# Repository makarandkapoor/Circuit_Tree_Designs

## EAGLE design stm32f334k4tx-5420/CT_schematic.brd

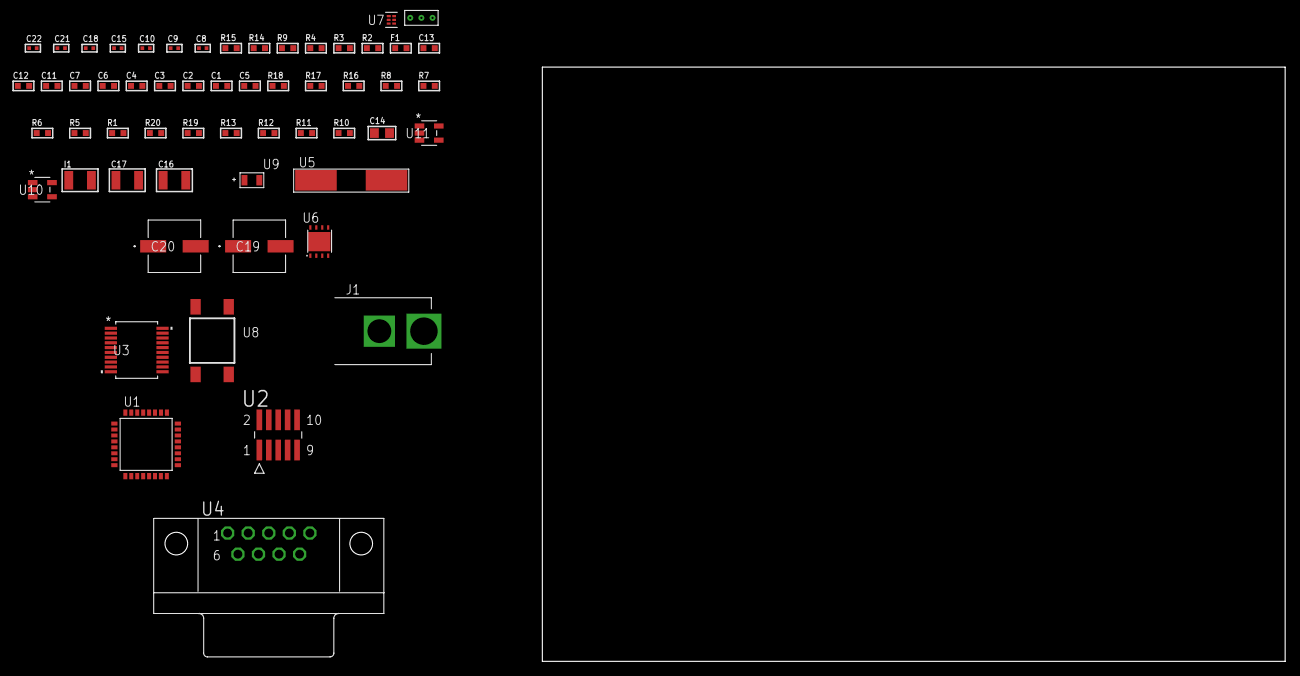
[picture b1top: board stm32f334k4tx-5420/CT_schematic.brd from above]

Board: 2 copper layers, 100.0 x 80.0 mm, 57 parts (0 on the bottom side), 40 nets, no tracks yet.

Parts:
C1, C2, C3, C4: 1e-07; C0603
C5: 4.7e-06; C0603
C6: 1e-08; C0603
C7, C11, C12, C13: 1e-06; C0603
C8, C9: 1e-11; C0402
C10, C18: 1e-07; C0402
C14: 4.7e-06; C0805
C15, C21, C22: 1e-08; C0402
C16, C17: 1e-05; C1210
C19, C20: 0.0001; EXV-9H
F1: 240.0; L0603
I1: 1.5e-05; L1210
J1: PJ-037B; PJ-037B_PACKAGE
R1, R5, R6, R7, R8, R16, R17: 10000.0; R0603
R2, R15: 1000.0; R0603
R3: 1270.0; R0603
R4: 4700.0; R0603
R9: 5.0; R0603
R10, R11, R12, R13: 100000.0; R0603
R14: 1500.0; R0603
R18: 18000.0; R0603
R19: 470000.0; R0603
R20: 120000.0; R0603
U1: STM32F334K4T6; LQFP32
U2: FTSH-105-01-L-DV-K; SAMTEC_FTSH-105-01-L-DV-K
U3: MAX3218EAP+T; SSOP-20
U4: 182-009-113R531; 182-009-MALE
U5: ABLS-25.000MHZ-B2F-T
U6: LP3878SDX-ADJ/NOPB; WSON-8
U7: TPS3895ADRYR; SON-6
U8: 4-1437565-2; SW_4-1437565-2
U9: Q65110A2395; LGM67K-G1J2-24-Z
U10, U11: nc7sz125m5x; NC7SZ125M5X
U12: Dummy; DUMMY_PACKAGE_115

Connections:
CLK_CRYSTAL_U1_2: C8.1, U1.2, U5.1
CLK_CRYSTAL_U1_3: C9.1, U1.3, U5.2
GND: C1.2, C2.2, C3.2, C4.2, C5.2, C6.2, C7.2, C8.2, C9.2, C10.2, C11.2, C12.2, C13.2, C15.2, C16.2, C17.2, C18.2, C19.2, C20.2, C21.2, C22.2, J1.2, R2.2, R5.2, R9.2, R15.2, R18.2, R20.2, U1.16, U1.32, U2.3, U2.5, U3.5, U3.17, U3.20, U4.5, U6.3, U6.PAD, U7.2, U9.C, U10.2, U10.3, U11.1, U11.3, U12.1
NET_U1_4: R4.1, U1.4, U11.4
NET_U1_5: C6.1, C7.1, F1.1, U1.5
NET_U1_29: R3.1, U1.29, U9.A
NET_U1_30: R1.1, U1.30, U8.3, U8.4
NET_U1_31: R5.1, U1.31
NET_U2_9: R9.1, U2.9
NET_U3_1: I1.1, U3.1
NET_U3_2: R10.1, U3.2
NET_U3_3: R11.1, U3.3
NET_U3_4: R12.1, U3.4
NET_U3_15: C13.1, U3.15
NET_U3_16: C14.2, U3.16
NET_U3_18: C14.1, U3.18
NET_U3_19: C12.1, U3.19
NET_U4_2: U3.12, U4.2
NET_U4_3: U3.14, U4.3
NET_U4_7: U3.11, U4.7
NET_U4_8: U3.13, U4.8
NET_U6_1: C15.1, U6.1
NET_U6_6: R14.2, R15.1, U6.6
NET_U6_8: R13.1, U6.8
NET_U7_1: R17.1, R18.1, U7.1
NET_U7_3: R19.2, R20.1, U7.3
NET_U7_4: R16.1, U7.4, U10.4, U11.2
NET_U8_1: R2.1, U8.1, U8.2
PROC_ADC1_IN1: U1.6, U12.3
PROC_ADC1_IN2: U1.7, U12.2
PROC_SYS_JTCK_SWCLK: R7.1, U1.24, U2.4
PROC_SYS_JTDO_TRACESWO: U1.26, U2.6
PROC_SYS_JTMS_SWDIO: R8.1, U1.23, U2.2
PROC_USART1_CTS: U1.21, U3.8
PROC_USART1_RTS: U1.22, U3.10
PROC_USART1_RX: U1.20, U3.9
PROC_USART1_TX: U1.19, U3.7
RST_OUT_U2_JTAG_RST_B: R6.1, U2.10, U10.1
VCC_S1_14V8: C16.1, C19.1, C20.1, J1.1, R13.2, U6.4
VCC_TIER1_2V5: C1.1, C2.1, C3.1, C4.1, C5.1, C10.1, C11.1, C17.1, C18.1, C21.1, C22.1, F1.2, I1.2, R1.2, R3.2, R4.2, R6.2, R7.2, R8.2, R10.2, R11.2, R12.2, R14.1, R16.2, R17.2, R19.1, U1.1, U1.17, U2.1, U3.6, U6.5, U7.6, U10.5, U11.5

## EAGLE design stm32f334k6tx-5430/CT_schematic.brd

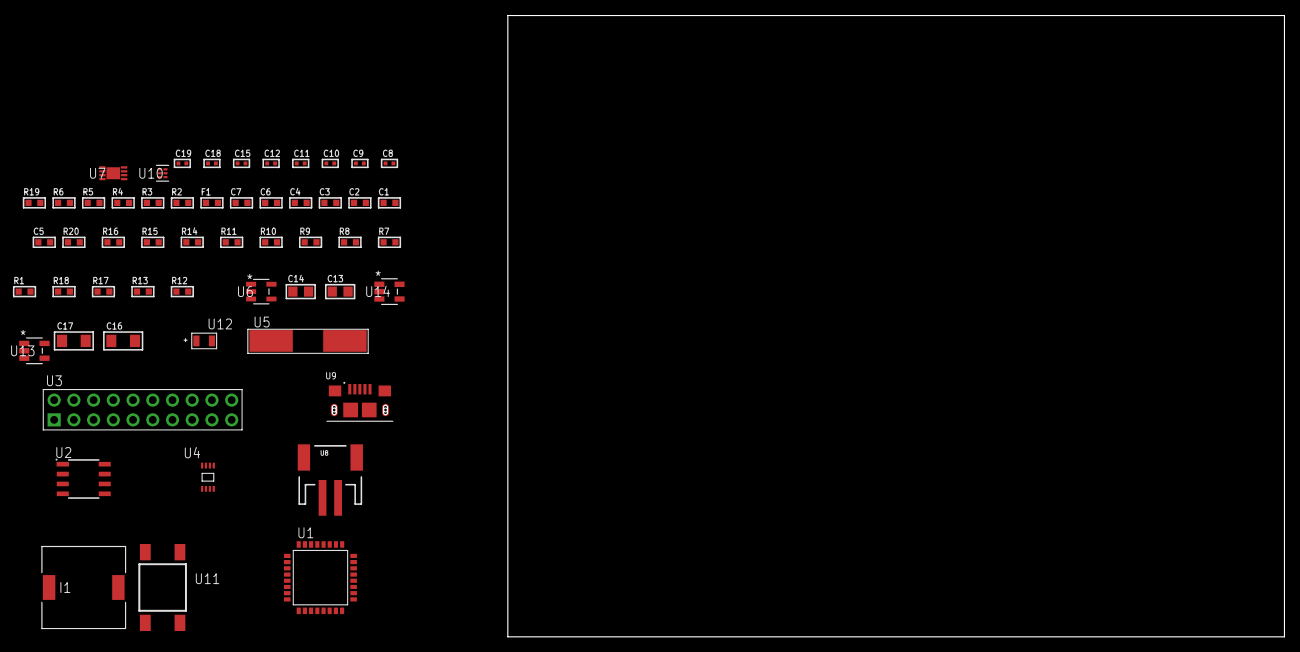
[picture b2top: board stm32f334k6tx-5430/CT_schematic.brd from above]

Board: 2 copper layers, 122.6 x 80.0 mm, 55 parts (0 on the bottom side), 32 nets, no tracks yet.

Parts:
C1, C2, C3, C4: 1e-07; C0603
C5: 4.7e-06; C0603
C6: 1e-08; C0603
C7: 1e-06; C0603
C8, C9: 1e-11; C0402
C10, C12, C18, C19: 1e-08; C0402
C11, C15: 1e-07; C0402
C13, C14: 1e-05; C0805
C16, C17: 1e-05; C1206
F1: 240.0; L0603
I1: 3.8e-06; DR1040
R1, R7, R8, R9, R10, R11, R14, R15, R20: 10000.0; R0603
R2: 1000.0; R0603
R3: 1270.0; R0603
R4: 4700.0; R0603
R5, R6: 2200.0; R0603
R12: 309473.68421053; R0603
R13: 1000000.0; R0603
R16: 18000.0; R0603
R17: 470000.0; R0603
R18: 120000.0; R0603
R19: 2000.0; R0603
U1: STM32F334K6T6; LQFP32
U2: AT25256B-SSHL-T; SOIC-8
U3: TST-110-05-T-D-RA
U4: 24AA02T-I/MNY; TDFN-8/6MM
U5: ABLS-25.000MHZ-B2F-T
U6: ltc3406es5; TSOT-23-5
U7: MCP73831T-2ACI/MC; DFN8_2X3MC
U8: S2B-PH-SM4-TB(LF)(SN); JST-2-SMD
U9: 10118193-0001LF; FCI_10118193-0001LF
U10: TPS3895ADRYR; SON-6
U11: 4-1437565-2; SW_4-1437565-2
U12: Q65110A2395; LGM67K-G1J2-24-Z
U13, U14: nc7sz125m5x; NC7SZ125M5X

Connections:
CLK_CRYSTAL_U1_2: C8.1, U1.2, U5.1
CLK_CRYSTAL_U1_3: C9.1, U1.3, U5.2
GND: C1.2, C2.2, C3.2, C4.2, C5.2, C6.2, C7.2, C8.2, C9.2, C10.2, C11.2, C12.2, C13.2, C14.1, C14.2, C15.2, C16.2, C17.2, C18.2, C19.2, R2.2, R7.2, R12.2, R16.2, R18.2, R19.2, U1.16, U1.32, U2.4, U3.4, U3.6, U3.8, U3.10, U3.12, U3.14, U3.16, U3.18, U3.20, U4.4, U4.7, U6.2, U7.6, U7.9, U8.2, U9.5, U9.6, U9.7, U9.8, U9.9, U10.2, U12.C, U13.2, U13.3, U14.1, U14.3
INPUT_USBPOWER_5V: C16.1, R20.2, U7.1, U7.2, U9.1
NET_U1_4: R4.1, U1.4, U14.4
NET_U1_5: C6.1, C7.1, F1.1, U1.5
NET_U1_25: R5.1, U1.25, U4.6
NET_U1_28: R3.1, U1.28, U12.A
NET_U1_29: R1.1, U1.29, U11.3, U11.4
NET_U1_30: R6.1, U1.30, U4.5
NET_U1_31: R7.1, U1.31
NET_U2_3: R8.1, U2.3
NET_U2_7: R10.1, U2.7
NET_U6_3: I1.1, U6.3
NET_U6_5: R12.1, R13.1, U6.5
NET_U6_ATNET_3: I1.2, R13.2
NET_U7_5: R20.1, U7.5
NET_U7_8: R19.1, U7.8
NET_U10_1: R15.1, R16.1, U10.1
NET_U10_3: R17.2, R18.1, U10.3
NET_U10_4: R14.1, U10.4, U13.4, U14.2
NET_U11_1: R2.1, U11.1, U11.2
PROC_SPI1_MISO: U1.12, U2.2
PROC_SPI1_MOSI: U1.13, U2.5
PROC_SPI1_NSS: R9.1, U1.10, U2.1
PROC_SPI1_SCK: U1.11, U2.6
PROC_SYS_JTCK_SWCLK: U1.24, U3.9
PROC_SYS_JTDO_TRACESWO: U1.26, U3.13
PROC_SYS_JTMS_SWDIO: U1.23, U3.7
RST_OUT_U3_SRESET_B: R11.1, U3.15, U13.1
VCC_S1_3V7: C13.1, C17.1, U6.4, U7.3, U7.4, U8.1
VCC_TIER1_2V5: C1.1, C2.1, C3.1, C4.1, C5.1, C10.1, C11.1, C12.1, C14.2, C15.1, C18.1, C19.1, F1.2, I1.2, R1.2, R3.2, R4.2, R5.2, R6.2, R8.2, R9.2, R10.2, R11.2, R13.2, R14.2, R15.2, R17.1, U1.1, U1.17, U2.8, U3.1, U4.8, U10.6, U13.5, U14.5

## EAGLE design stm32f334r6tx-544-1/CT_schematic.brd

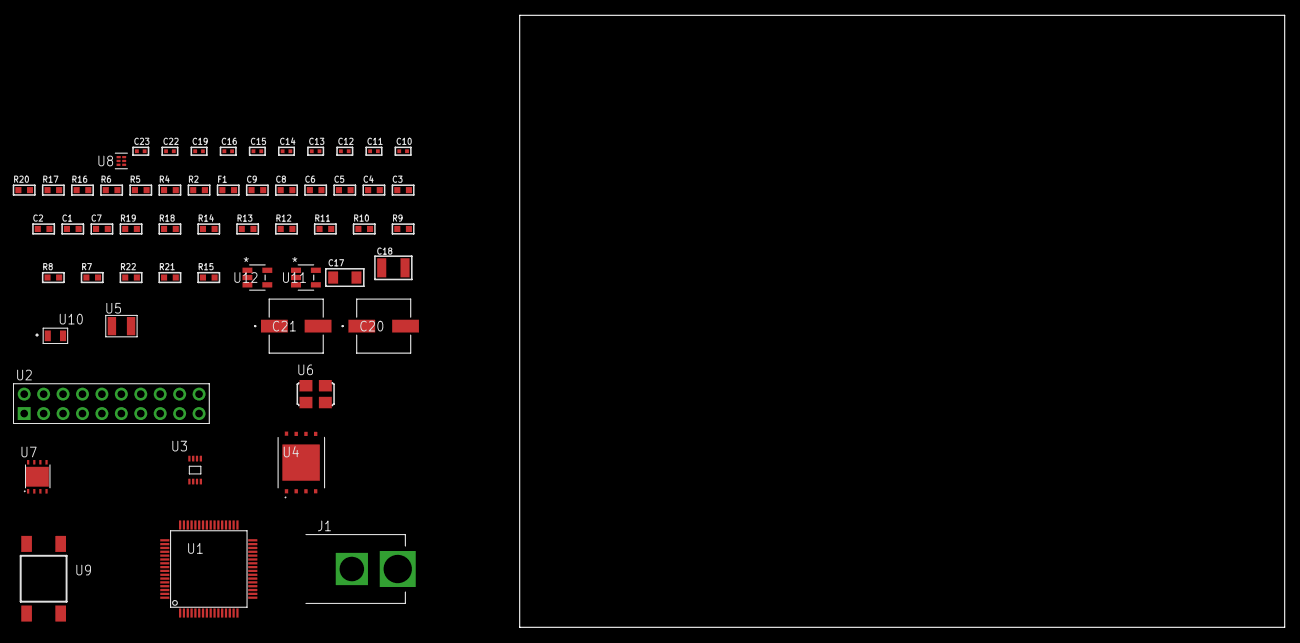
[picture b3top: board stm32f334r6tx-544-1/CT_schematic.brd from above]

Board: 2 copper layers, 100.0 x 80.0 mm, 57 parts (0 on the bottom side), 32 nets, no tracks yet.

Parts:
C1, C9: 1e-06; C0603
C2, C3, C4, C5, C6: 1e-07; C0603
C7: 4.7e-06; C0603
C8: 1e-08; C0603
C10, C11: 1e-11; C0402
C12, C19: 1e-07; C0402
C13, C14, C15, C16, C22, C23: 1e-08; C0402
C17: 1e-05; C1206
C18: 1e-05; C1210
C20, C21: 0.0001; EXV-9H
F1: 240.0; L0603
J1: PJ-037B; PJ-037B_PACKAGE
R2, R17: 1000.0; R0603
R4: 4700.0; R0603
R5, R6: 2200.0; R0603
R7, R8, R9, R10, R11, R12, R13, R14, R18, R19: 10000.0; R0603
R15: 100000.0; R0603
R16: 2231.0; R0603
R20: 9100.0; R0603
R21: 680000.0; R0603
R22: 120000.0; R0603
U1: STM32F334R6T6; LQFP64
U2: TST-110-05-T-D-RA
U3: 24AA64T-I/MNY; TDFN-8/6MM
U4: S25FL128SDPNFI001; WNG008
U5: ABS07-32.768KHZ-7-T
U6: ASFL1-25MHZ-NCS; ASFL1
U7: LP3878SDX-ADJ/NOPB; WSON-8
U8: TPS3895ADRYR; SON-6
U9: 4-1437565-2; SW_4-1437565-2
U10: Q65110A2395; LGM67K-G1J2-24-Z
U11, U12: nc7sz125m5x; NC7SZ125M5X

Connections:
CLK_CRYSTAL_U1_3: C10.1, U1.3, U5.1
CLK_CRYSTAL_U1_4: C11.1, U1.4, U5.2
CLK_U1_5: U1.5, U6.3
GND: C1.2, C2.2, C3.2, C4.2, C5.2, C6.2, C7.2, C8.2, C9.2, C10.2, C11.2, C12.2, C13.2, C14.2, C15.2, C16.2, C17.2, C18.2, C19.2, C20.2, C21.2, C22.2, C23.2, J1.2, R2.2, R7.2, R11.2, R17.2, R20.2, R22.2, U1.12, U1.18, U1.31, U1.47, U1.63, U2.4, U2.6, U2.8, U2.10, U2.12, U2.14, U2.16, U2.18, U2.20, U3.4, U3.7, U4.4, U4.PAD, U6.2, U7.3, U7.PAD, U8.2, U10.C, U11.2, U11.3, U12.1, U12.3
NET_U1_7: R4.1, U1.7, U12.4
NET_U1_13: C8.1, C9.1, F1.1, U1.13
NET_U1_50: R5.1, U1.50, U3.6
NET_U1_59: R6.1, U1.59, U3.5
NET_U1_60: R7.1, U1.60
NET_U1_62: U9.3, U9.4
NET_U3_1: R9.1, U3.1
NET_U3_2: R10.1, U3.2
NET_U3_3: R11.1, U3.3
NET_U4_3: R12.1, U4.3
NET_U4_7: R14.1, U4.7
NET_U7_1: C16.1, U7.1
NET_U7_6: R16.2, R17.1, U7.6
NET_U7_8: R15.1, U7.8
NET_U8_1: R19.1, R20.1, U8.1
NET_U8_3: R21.2, R22.1, U8.3
NET_U8_4: R18.1, U8.4, U11.4, U12.2
NET_U9_1: R2.1, U9.1, U9.2
PROC_SPI1_MISO: U1.22, U4.2
PROC_SPI1_MOSI: U1.23, U4.5
PROC_SPI1_NSS: R13.1, U1.20, U4.1
PROC_SPI1_SCK: U1.21, U4.6
PROC_SYS_JTCK_SWCLK: U1.49, U2.9
PROC_SYS_JTDO_TRACESWO: U1.55, U2.13
PROC_SYS_JTMS_SWDIO: U1.46, U2.7
RST_OUT_U2_SRESET_B: R8.1, U2.15, U11.1
VCC_S1_8V4: C17.1, C20.1, C21.1, J1.1, R15.2, U7.4
VCC_TIER1_3V3: C1.1, C2.1, C3.1, C4.1, C5.1, C6.1, C7.1, C12.1, C13.1, C14.1, C15.1, C18.1, C19.1, C22.1, C23.1, F1.2, R4.2, R5.2, R6.2, R8.2, R9.2, R10.2, R12.2, R13.2, R14.2, R16.1, R18.2, R19.2, R21.1, U1.1, U1.19, U1.32, U1.48, U1.64, U2.1, U3.8, U4.8, U6.4, U7.5, U8.6, U11.5, U12.5

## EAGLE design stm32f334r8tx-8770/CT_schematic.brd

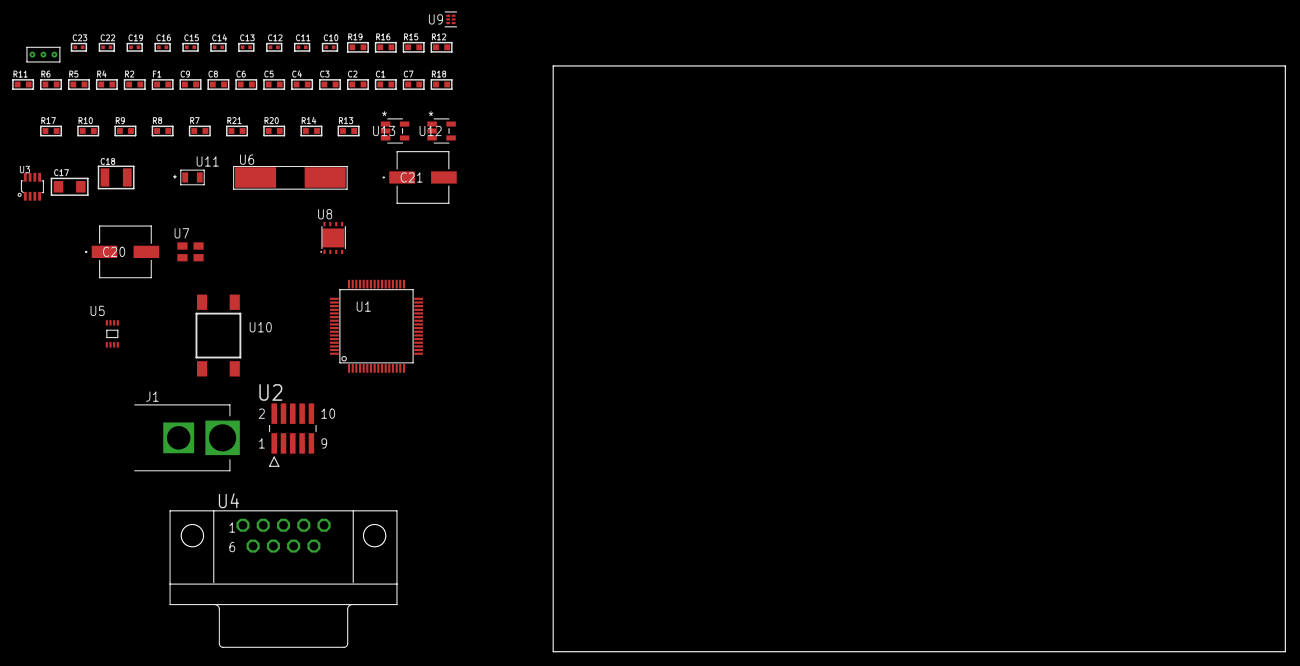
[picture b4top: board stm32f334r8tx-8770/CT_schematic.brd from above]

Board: 2 copper layers, 100.0 x 80.0 mm, 58 parts (0 on the bottom side), 32 nets, no tracks yet.

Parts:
C1, C9: 1e-06; C0603
C2, C3, C4, C5, C6: 1e-07; C0603
C7: 4.7e-06; C0603
C8: 1e-08; C0603
C10, C11: 1e-11; C0402
C12, C13, C19: 1e-07; C0402
C14, C15, C16, C22, C23: 1e-08; C0402
C17: 1e-05; C1206
C18: 1e-05; C1210
C20, C21: 0.0001; EXV-9H
F1: 240.0; L0603
J1: PJ-037B; PJ-037B_PACKAGE
R2, R16: 1000.0; R0603
R4: 4700.0; R0603
R5, R6: 2200.0; R0603
R7, R8, R9, R10, R17, R18: 10000.0; R0603
R11: 5.0; R0603
R12: 120.0; R0603
R13, R14: 100000.0; R0603
R15: 2231.0; R0603
R19: 9100.0; R0603
R20: 680000.0; R0603
R21: 120000.0; R0603
U1: STM32F334R8T6; LQFP64
U2: FTSH-105-01-L-DV-K; SAMTEC_FTSH-105-01-L-DV-K
U3: MAX3051EKA+T; SOT-23-8
U4: 182-009-113R531; 182-009-MALE
U5: 24AA01T-I/MNY; TDFN-8/6MM
U6: ABLS-25.000MHZ-B2F-T
U7: ASEK-32.768KHz-ECST; ASEK
U8: LP3878SDX-ADJ/NOPB; WSON-8
U9: TPS3895ADRYR; SON-6
U10: 4-1437565-2; SW_4-1437565-2
U11: Q65110A2395; LGM67K-G1J2-24-Z
U12, U13: nc7sz125m5x; NC7SZ125M5X
U14: Dummy; DUMMY_PACKAGE_126

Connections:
CLK_CRYSTAL_U1_5: C10.1, U1.5, U6.1
CLK_CRYSTAL_U1_6: C11.1, U1.6, U6.2
CLK_U1_3: U1.3, U7.3
GND: C1.2, C2.2, C3.2, C4.2, C5.2, C6.2, C7.2, C8.2, C9.2, C10.2, C11.2, C12.2, C13.2, C14.2, C15.2, C16.2, C17.2, C18.2, C19.2, C20.2, C21.2, C22.2, C23.2, J1.2, R2.2, R7.2, R11.2, R13.2, R16.2, R19.2, R21.2, U1.12, U1.18, U1.31, U1.47, U1.63, U2.3, U2.5, U3.2, U4.5, U5.4, U5.7, U7.2, U8.3, U8.PAD, U9.2, U11.C, U12.2, U12.3, U13.1, U13.3, U14.1
NET_U1_7: R4.1, U1.7, U13.4
NET_U1_13: C8.1, C9.1, F1.1, U1.13
NET_U1_50: R5.1, U1.50, U5.6
NET_U1_59: R6.1, U1.59, U5.5
NET_U1_60: R7.1, U1.60
NET_U1_62: U10.3, U10.4
NET_U2_9: R11.1, U2.9
NET_U3_6: R12.2, U3.6
NET_U3_8: R13.1, U3.8
NET_U4_2: R12.2, U3.6, U4.2
NET_U4_3: R12.1, U3.7, U4.3
NET_U8_1: C16.1, U8.1
NET_U8_6: R15.2, R16.1, U8.6
NET_U8_8: R14.1, U8.8
NET_U9_1: R18.1, R19.1, U9.1
NET_U9_3: R20.2, R21.1, U9.3
NET_U9_4: R17.1, U9.4, U12.4, U13.2
NET_U10_1: R2.1, U10.1, U10.2
PROC_CAN_RX: U1.44, U3.4
PROC_CAN_TX: U1.45, U3.1
PROC_SYS_JTCK_SWCLK: R9.1, U1.49, U2.4
PROC_SYS_JTDO_TRACESWO: U1.55, U2.6
PROC_SYS_JTMS_SWDIO: R10.1, U1.46, U2.2
PROC_TIM1_CH2: U1.9, U14.2
PROC_TIM1_CH4: U1.11, U14.3
RST_OUT_U2_JTAG_RST_B: R8.1, U2.10, U12.1
VCC_S1_10V2: C17.1, C20.1, C21.1, J1.1, R14.2, U8.4
VCC_TIER1_3V3: C1.1, C2.1, C3.1, C4.1, C5.1, C6.1, C7.1, C12.1, C13.1, C14.1, C15.1, C18.1, C19.1, C22.1, C23.1, F1.2, R4.2, R5.2, R6.2, R8.2, R9.2, R10.2, R15.1, R17.2, R18.2, R20.1, U1.1, U1.19, U1.32, U1.48, U1.64, U2.1, U3.3, U5.8, U7.4, U8.5, U9.6, U12.5, U13.5

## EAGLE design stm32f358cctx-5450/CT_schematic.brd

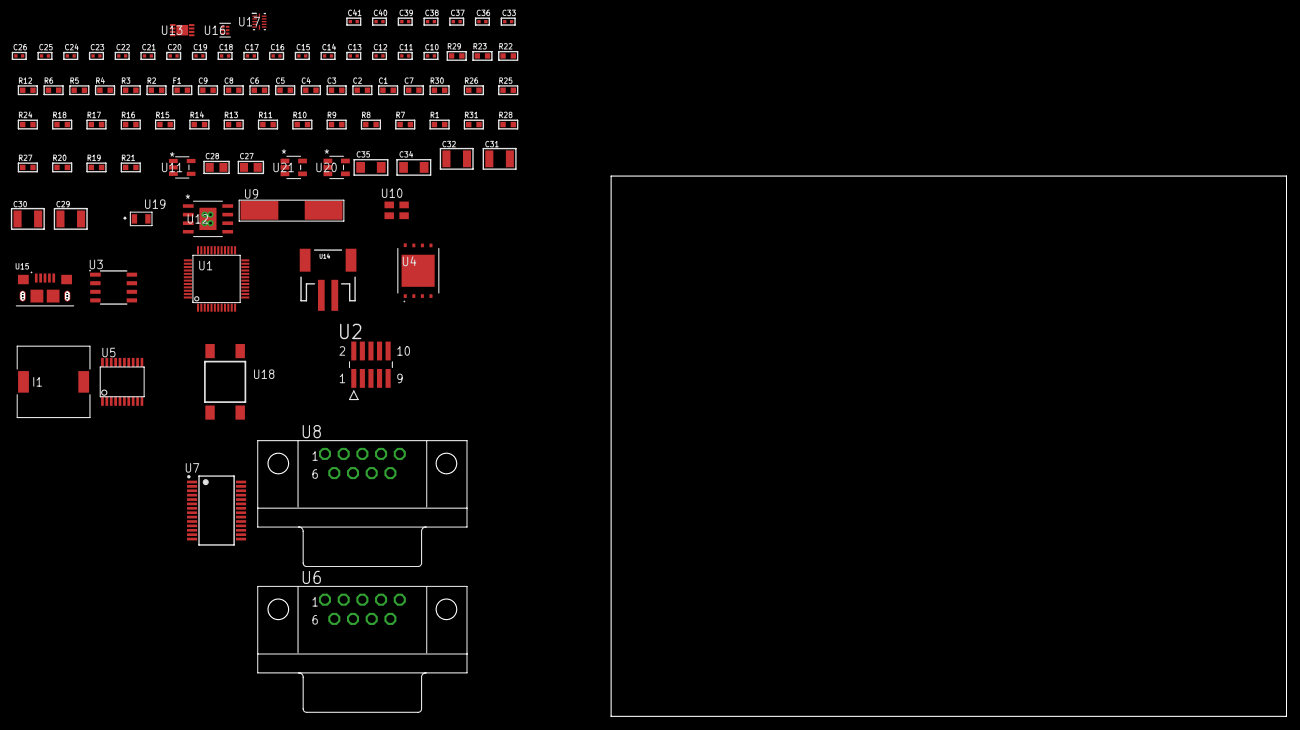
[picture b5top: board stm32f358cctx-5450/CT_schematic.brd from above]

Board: 2 copper layers, 95 parts (0 on the bottom side), 74 nets, no tracks yet.

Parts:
C1, C9: 1e-06; C0603
C2, C3, C4, C5, C6: 1e-07; C0603
C7: 4.7e-06; C0603
C8: 1e-08; C0603
C10, C11: 1e-11; C0402
C12, C15, C16, C17, C18, C19, C20, C21, C22, C23, C24, C25, C33, C37, C39: 1e-07; C0402
C13, C14, C26, C36, C38, C40, C41: 1e-08; C0402
C27, C28: 1e-05; C0805
C29, C30, C31, C32: 1e-05; C1210
C34, C35: 1e-05; C1206
F1: 240.0; L0603
I1: 5.2e-06; DR1040
R1, R7, R8, R9, R10, R11, R13, R14, R15, R16, R17, R18, R24, R25, R30: 10000.0; R0603
R2: 1000.0; R0603
R3: 910.0; R0603
R4: 4700.0; R0603
R5, R6, R23: 2200.0; R0603
R12: 5.0; R0603
R19: 100000.0; R0603
R20: 490000.0; R0603
R21: 1000000.0; R0603
R22: 3600.0; R0603
R26: 82000.0; R0603
R27: 300000.0; R0603
R28: 120000.0; R0603
R29: 2000.0; R0603
R31: 200000.0; R0603
U1: STM32F358CCT6; LQFP48
U2: FTSH-105-01-L-DV-K; SAMTEC_FTSH-105-01-L-DV-K
U3: 24AA1025T-I/SN; SOIC-8
U4: S25FL128SDPNFI001; WNG008
U5: SP3203ECY-L/TR; TSSOP20-I
U6, U8: 182-009-113R531; 182-009-MALE
U7: ST3241EBPR; SSOP-28
U9: ABLS-25.000MHZ-B2F-T
U10: ASEK-2-32.768KHz-ECST; ASEK
U11: ltc3406es5; TSOT-23-5
U12: MIC5234YME; SOIC-8_EP
U13: MCP73831T-2ACI/MC; DFN8_2X3MC
U14: S2B-PH-SM4-TB(LF)(SN); JST-2-SMD
U15: 10118193-0001LF; FCI_10118193-0001LF
U16: TPS3895ADRYR; SON-6
U17: LSF0204DRUTR; RUT0012A
U18: 4-1437565-2; SW_4-1437565-2
U19: Q65110A2395; LGM67K-G1J2-24-Z
U20, U21: nc7sz125m5x; NC7SZ125M5X

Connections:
CLK_CRYSTAL_U1_5: C10.1, U1.5, U9.1
CLK_CRYSTAL_U1_6: C11.1, U1.6, U9.2
CLK_U1_3: U1.3, U10.3
GND: C1.2, C2.2, C3.2, C4.2, C5.2, C6.2, C7.2, C8.2, C9.2, C10.2, C11.2, C12.2, C13.2, C14.2, C15.2, C16.2, C19.2, C20.2, C21.2, C24.2, C25.2, C26.2, C27.2, C28.1, C28.2, C29.2, C30.2, C31.2, C32.2, C33.2, C34.2, C35.2, C36.2, C37.2, C38.2, C39.2, C40.2, C41.2, R2.2, R7.2, R8.2, R12.2, R15.2, R20.2, R23.2, R26.2, R28.2, R29.2, U1.8, U1.23, U1.35, U1.47, U2.3, U2.5, U3.4, U4.4, U4.PAD, U5.18, U6.5, U7.23, U7.25, U8.5, U10.2, U11.2, U12.7, U12.EPAD, U13.6, U13.9, U14.2, U15.5, U15.6, U15.7, U15.8, U15.9, U16.2, U17.6, U19.C, U20.2, U20.3, U21.1, U21.3
INPUT_USBPOWER_5V: C34.1, R30.2, U13.1, U13.2, U15.1
NET_U1_7: R4.1, U1.7, U21.4
NET_U1_9: C8.1, C9.1, F1.1, U1.9
NET_U1_20: R8.1, U1.20
NET_U1_38: R5.1, U1.38, U3.6
NET_U1_43: R6.1, U1.43, U3.5
NET_U1_44: R7.1, U1.44
NET_U1_45: R3.1, U1.45, U19.A
NET_U1_46: R1.1, U1.46, U18.3, U18.4
NET_U2_9: R12.1, U2.9
NET_U3_1: R14.1, U3.1
NET_U3_2: R15.1, U3.2
NET_U3_3: R13.1, U3.3
NET_U4_3: R16.1, U4.3
NET_U4_7: R18.1, U4.7
NET_U5_1: C17.1, U5.1
NET_U5_2: C19.1, U5.2
NET_U5_3: C17.2, U5.3
NET_U5_4: C18.1, U5.4
NET_U5_5: C18.2, U5.5
NET_U5_6: C20.1, U5.6
NET_U6_2: U5.14, U6.2
NET_U6_3: U5.17, U6.3
NET_U6_7: U5.13, U6.7
NET_U6_8: U5.16, U6.8
NET_U7_1: C23.1, U7.1
NET_U7_2: C23.2, U7.2
NET_U7_3: C25.1, U7.3
NET_U7_22: R19.1, U7.22
NET_U7_24: C22.2, U7.24
NET_U7_27: C24.1, U7.27
NET_U7_28: C22.1, U7.28
NET_U8_2: U7.4, U8.2
NET_U8_3: U7.9, U8.3
NET_U8_7: U7.5, U8.7
NET_U8_8: U7.10, U8.8
NET_U11_3: I1.1, U11.3
NET_U11_5: R20.1, R21.1, U11.5
NET_U11_ATNET_3: I1.2, R21.2
NET_U12_4: R22.2, R23.1, U12.4
NET_U13_5: R30.1, U13.5
NET_U13_8: R29.1, U13.8
NET_U16_1: R25.1, R26.1, U16.1
NET_U16_3: R27.2, R28.1, U16.3
NET_U16_4: R24.1, U16.4, U20.4, U21.2
NET_U17_12: R31.1, U17.12
NET_U18_1: R2.1, U18.1, U18.2
PROC_SPI1_MISO: U1.16, U4.2
PROC_SPI1_MOSI: U1.17, U4.5
PROC_SPI1_NSS: R17.1, U1.14, U4.1
PROC_SPI1_SCK: U1.15, U4.6
PROC_SYS_JTCK_SWCLK: R10.1, U1.37, U2.4
PROC_SYS_JTDO_TRACESWO: U1.39, U2.6
PROC_SYS_JTMS_SWDIO: R11.1, U1.34, U2.2
PROC_USART1_CTS: U1.32, U5.8
PROC_USART1_RTS: U1.33, U5.10
PROC_USART1_RX: U1.31, U5.11
PROC_USART1_TX: U1.30, U5.7
PROC_USART2_CTS_TOIOBUF: U1.10, U17.2
PROC_USART2_CTS_TOXCVR: U7.13, U17.10
PROC_USART2_RTS_TOIOBUF: U1.11, U17.4
PROC_USART2_RTS_TOXCVR: U7.18, U17.8
PROC_USART2_RX_TOIOBUF: U1.13, U17.5
PROC_USART2_RX_TOXCVR: U7.19, U17.7
PROC_USART2_TX_TOIOBUF: U1.12, U17.3
PROC_USART2_TX_TOXCVR: U7.14, U17.9
RST_OUT_U2_JTAG_RST_B: R9.1, U2.10, U20.1
VCC_S1_3V7: C27.1, C29.1, C30.1, C35.1, U11.4, U12.5, U12.8, U13.3, U13.4, U14.1
VCC_TIER1_1V8: C1.1, C2.1, C3.1, C4.1, C5.1, C6.1, C7.1, C12.1, C13.1, C14.1, C16.1, C26.1, C28.2, C33.1, C38.1, C39.1, C40.1, C41.1, F1.2, I1.2, R1.2, R3.2, R4.2, R5.2, R6.2, R9.2, R10.2, R11.2, R13.2, R14.2, R16.2, R17.2, R18.2, R21.2, R24.2, R25.2, R27.1, R31.2, U1.1, U1.24, U1.36, U1.48, U2.1, U3.7, U3.8, U4.8, U5.12, U10.4, U16.6, U17.1, U20.5, U21.5
VCC_TIER1_3V0: C15.1, C21.1, C31.1, C32.1, C36.1, C37.1, R19.2, R22.1, U5.19, U7.26, U12.1, U17.11

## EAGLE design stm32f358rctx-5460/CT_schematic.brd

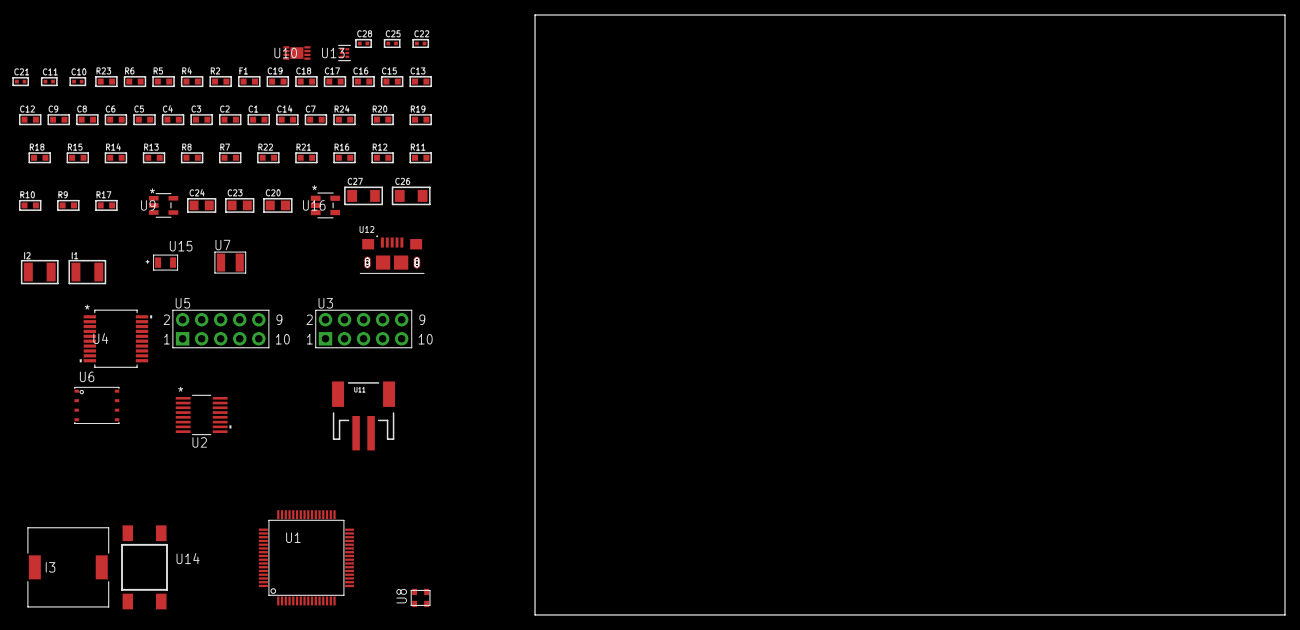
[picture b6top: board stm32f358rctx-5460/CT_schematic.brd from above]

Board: 2 copper layers, 122.6 x 80.0 mm, 70 parts (0 on the bottom side), 51 nets, no tracks yet.

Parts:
C1, C9, C12, C13, C15, C16, C17, C18, C19: 1e-06; C0603
C2, C3, C4, C5, C6: 1e-07; C0603
C7: 4.7e-06; C0603
C8: 1e-08; C0603
C10, C11: 1e-11; C0402
C14: 2.2e-07; C0603
C20: 4.7e-06; C0805
C21, C22, C28: 1e-08; C0402
C23, C24: 1e-05; C0805
C25: 1e-07; C0402
C26, C27: 1e-05; C1206
F1: 240.0; L0603
I1: 1e-05; L1210
I2: 1.5e-05; L1210
I3: 5.2e-06; DR1040
R2: 1000.0; R0603
R4: 4700.0; R0603
R5, R6: 2200.0; R0603
R7, R8, R13, R14, R15, R18, R19, R24: 10000.0; R0603
R9, R10, R11, R12: 100000.0; R0603
R16: 490000.0; R0603
R17: 1000000.0; R0603
R20: 82000.0; R0603
R21: 300000.0; R0603
R22: 120000.0; R0603
R23: 2000.0; R0603
U1: STM32F358RCT6; LQFP64
U2: LTC2804CGN-1#PBF; SSOP-16
U3, U5: HTSS-105-01-G-D
U4: MAX3218EAP+T; SSOP-20
U6: 24AA512-I/MF; DFN8-S
U7: ABS07-32.768KHZ-7-T
U8: ASDMB-25.000MHZ-EC-T; ASDMB-XX.XXXXMHZ-XX-XX-XXX
U9: ltc3406es5; TSOT-23-5
U10: MCP73831T-2ACI/MC; DFN8_2X3MC
U11: S2B-PH-SM4-TB(LF)(SN); JST-2-SMD
U12: 10118193-0001LF; FCI_10118193-0001LF
U13: TPS3895ADRYR; SON-6
U14: 4-1437565-2; SW_4-1437565-2
U15: Q65110A2395; LGM67K-G1J2-24-Z
U16: nc7sz125m5x; NC7SZ125M5X

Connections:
CLK_CRYSTAL_U1_3: C10.1, U1.3, U7.1
CLK_CRYSTAL_U1_4: C11.1, U1.4, U7.2
CLK_U1_5: U1.5, U8.3
GND: C1.2, C2.2, C3.2, C4.2, C5.2, C6.2, C7.2, C8.2, C9.2, C10.2, C11.2, C12.2, C13.2, C15.2, C16.2, C17.2, C18.2, C19.2, C21.2, C22.2, C23.2, C24.1, C24.2, C25.2, C26.2, C27.2, C28.2, R2.2, R7.2, R8.2, R15.2, R16.2, R20.2, R22.2, R23.2, U1.12, U1.31, U1.47, U1.63, U2.8, U3.9, U4.5, U4.17, U4.20, U5.9, U6.4, U8.2, U9.2, U10.6, U10.9, U11.2, U12.5, U12.6, U12.7, U12.8, U12.9, U13.2, U15.C, U16.1, U16.3
INPUT_USBPOWER_5V: C26.1, R24.2, U10.1, U10.2, U12.1
NET_U1_7: R4.1, U1.7, U16.4
NET_U1_13: C8.1, C9.1, F1.1, U1.13
NET_U1_28: R8.1, U1.28
NET_U1_49: R6.1, U1.49, U6.5
NET_U1_50: R5.1, U1.50, U6.6
NET_U1_60: R7.1, U1.60
NET_U1_62: U14.3, U14.4
NET_U2_6: C12.1, U2.6
NET_U2_7: C14.1, I1.2, U2.7
NET_U2_9: C13.1, U2.9
NET_U2_10: C14.2, U2.10
NET_U2_11: R9.1, U2.11
NET_U3_3: U2.1, U3.3
NET_U3_4: U2.2, U3.4
NET_U3_5: U2.3, U3.5
NET_U3_6: U2.4, U3.6
NET_U4_1: I2.1, U4.1
NET_U4_2: R10.1, U4.2
NET_U4_3: R11.1, U4.3
NET_U4_4: R12.1, U4.4
NET_U4_15: C19.1, U4.15
NET_U4_16: C20.2, U4.16
NET_U4_18: C20.1, U4.18
NET_U4_19: C18.1, U4.19
NET_U5_3: U4.12, U5.3
NET_U5_4: U4.11, U5.4
NET_U5_5: U4.14, U5.5
NET_U5_6: U4.13, U5.6
NET_U6_1: R13.1, U6.1
NET_U6_2: R14.1, U6.2
NET_U6_3: R15.1, U6.3
NET_U9_3: I3.1, U9.3
NET_U9_5: R16.1, R17.1, U9.5
NET_U9_ATNET_3: I3.2, R17.2
NET_U10_5: R24.1, U10.5
NET_U10_8: R23.1, U10.8
NET_U13_1: R19.1, R20.1, U13.1
NET_U13_3: R21.2, R22.1, U13.3
NET_U13_4: R18.1, U13.4, U16.2
NET_U14_1: R2.1, U14.1, U14.2
PROC_UART4_RX: U1.52, U2.16
PROC_UART4_TX: U1.51, U2.14
PROC_UART5_RX: U1.54, U4.9
PROC_UART5_TX: U1.53, U4.7
VCC_S1_3V7: C23.1, C27.1, U9.4, U10.3, U10.4, U11.1
VCC_TIER1_1V8: C1.1, C2.1, C3.1, C4.1, C5.1, C6.1, C7.1, C15.1, C16.1, C17.1, C21.1, C22.1, C24.2, C25.1, C28.1, F1.2, I1.1, I2.2, I3.2, R4.2, R5.2, R6.2, R9.2, R10.2, R11.2, R12.2, R13.2, R14.2, R17.2, R18.2, R19.2, R21.1, U1.1, U1.19, U1.32, U1.48, U1.64, U2.5, U2.12, U4.6, U6.7, U6.8, U8.4, U13.6, U16.5

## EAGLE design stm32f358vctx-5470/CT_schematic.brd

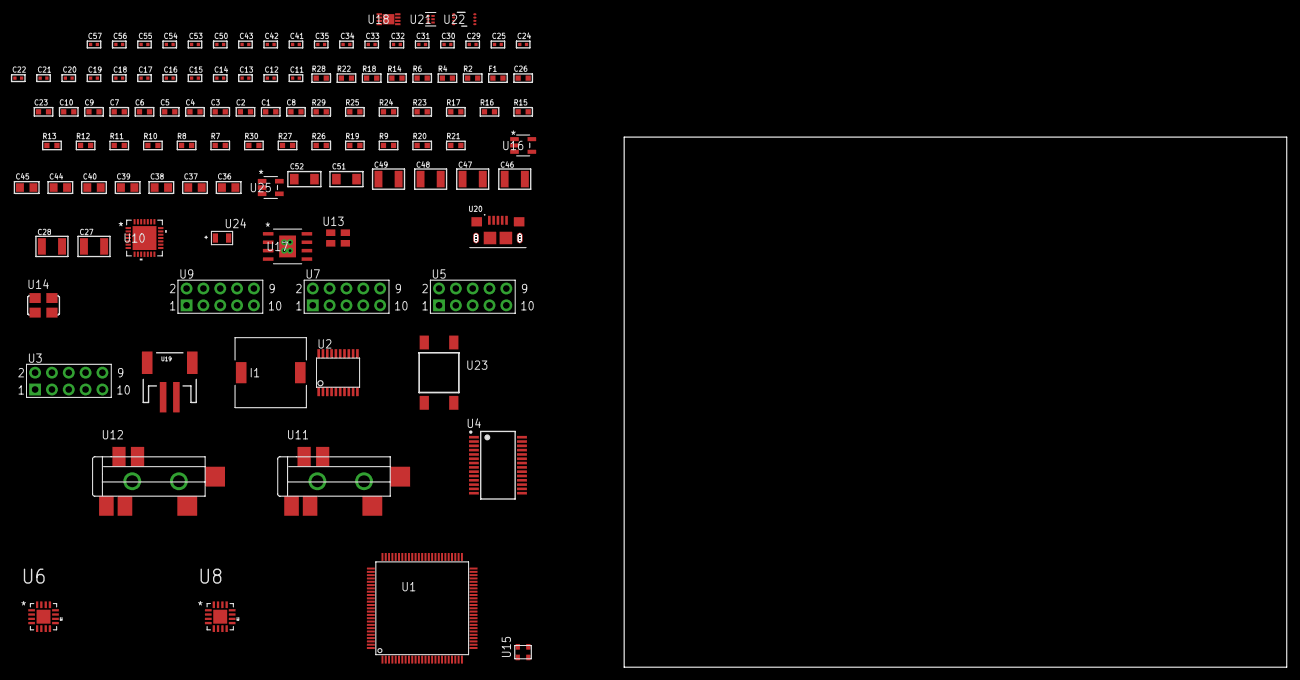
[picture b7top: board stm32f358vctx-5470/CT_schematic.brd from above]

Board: 2 copper layers, 122.6 x 80.0 mm, 111 parts (0 on the bottom side), 75 nets, no tracks yet.

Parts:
C1, C10, C23, C26: 1e-06; C0603
C2, C3, C4, C5, C6, C7: 1e-07; C0603
C8: 4.7e-06; C0603
C9: 1e-08; C0603
C11, C12, C13, C14, C15, C16, C17, C18, C19, C20, C21, C22, C24, C25, C31, C32, C33, C34, C35, C50, C54, C56: 1e-07; C0402
C27, C28: 2.2e-05; C1210
C29, C30: 1e-09; C0402
C36, C37, C38, C39, C40, C44, C45: 1e-05; C0805
C41, C42, C43, C53, C55, C57: 1e-08; C0402
C46, C47, C48, C49: 1e-05; C1210
C51, C52: 1e-05; C1206
F1: 240.0; L0603
I1: 3.8e-06; DR1040
R2: 1000.0; R0603
R4: 4700.0; R0603
R6, R22: 2200.0; R0603
R7, R8, R10, R11, R12, R13, R23, R24, R29: 10000.0; R0603
R9: 100000.0; R0603
R14: 47.0; R0603
R15, R16, R17: 47000.0; R0603
R18: 680.0; R0603
R19: 490000.0; R0603
R20: 1000000.0; R0603
R21: 4031.5447154472; R0603
R25: 82000.0; R0603
R26: 300000.0; R0603
R27: 120000.0; R0603
R28: 2000.0; R0603
R30: 200000.0; R0603
U1: STM32F358VCT6; LQFP100
U2: SP3203ECY-L/TR; TSSOP20-I
U3, U5, U7, U9: HTSS-105-01-G-D
U4: ST3241EBPR; SSOP-28
U6: TSC2008TRGVRQ1; QFN65P400X400X100-17N
U8: TSC2013QRSARQ1; QFN65P400X400X100-17N
U10: WM8731CLSEFL; QFN-28
U11, U12: SJ-43515TS-SMT-TR
U13: ASEK-2-32.768KHz-ECST; ASEK
U14: ASFL1-12.288MHZ-EC-T; ASFL1
U15: ASDMB-25.000MHZ-EC-T; ASDMB-XX.XXXXMHZ-XX-XX-XXX
U16: ltc3406es5; TSOT-23-5
U17: MIC5234YME; SOIC-8_EP
U18: MCP73831T-2ACI/MC; DFN8_2X3MC
U19: S2B-PH-SM4-TB(LF)(SN); JST-2-SMD
U20: 10118193-0001LF; FCI_10118193-0001LF
U21: TPS3895ADRYR; SON-6
U22: LSF0102DCTR; DCU0008A_N
U23: 4-1437565-2; SW_4-1437565-2
U24: Q65110A2395; LGM67K-G1J2-24-Z
U25: nc7sz125m5x; NC7SZ125M5X

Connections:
CLK_U1_8: U1.8, U13.3
CLK_U1_12: U1.12, U15.3
CLK_U10_1: U10.1, U14.3
GND: C1.2, C2.2, C3.2, C4.2, C5.2, C6.2, C7.2, C8.2, C9.2, C10.2, C11.2, C12.2, C15.2, C16.2, C17.2, C20.2, C21.2, C22.2, C23.2, C30.2, C31.2, C32.2, C33.2, C34.2, C35.2, C36.2, C37.2, C38.2, C39.2, C40.2, C41.2, C42.2, C43.2, C44.2, C45.1, C45.2, C46.2, C47.2, C48.2, C49.2, C50.2, C51.2, C52.2, C53.2, C54.2, C55.2, C56.2, C57.2, R2.2, R7.2, R8.2, R15.2, R16.2, R17.2, R19.2, R22.2, R25.2, R27.2, R28.2, U1.20, U1.49, U1.74, U1.99, U2.18, U3.9, U4.23, U4.25, U5.9, U6.10, U6.12, U6.17, U7.9, U8.17, U9.9, U10.4, U10.15, U10.19, U10.25, U10.26, U10.29, U11.1, U12.1, U13.2, U14.2, U15.2, U16.2, U17.7, U17.EPAD, U18.6, U18.9, U19.2, U20.5, U20.6, U20.7, U20.8, U20.9, U21.2, U22.1, U24.C, U25.1, U25.3
INPUT_USBPOWER_5V: C51.1, R29.2, U18.1, U18.2, U20.1
NET_U1_14: R4.1, U1.14, U25.4
NET_U1_22: C9.1, C10.1, F1.1, U1.21, U1.22
NET_U1_37: R8.1, U1.37
NET_U1_76: R6.1, U1.76, U8.1
NET_U1_94: R7.1, U1.94
NET_U1_98: U23.3, U23.4
NET_U2_1: C13.1, U2.1
NET_U2_2: C15.1, U2.2
NET_U2_3: C13.2, U2.3
NET_U2_4: C14.1, U2.4
NET_U2_5: C14.2, U2.5
NET_U2_6: C16.1, U2.6
NET_U3_3: U2.14, U3.3
NET_U3_4: U2.13, U3.4
NET_U3_5: U2.17, U3.5
NET_U3_6: U2.16, U3.6
NET_U4_1: C19.1, U4.1
NET_U4_2: C19.2, U4.2
NET_U4_3: C21.1, U4.3
NET_U4_22: R9.1, U4.22
NET_U4_24: C18.2, U4.24
NET_U4_27: C20.1, U4.27
NET_U4_28: C18.1, U4.28
NET_U5_3: U4.4, U5.3
NET_U5_4: U4.5, U5.4
NET_U5_5: U4.9, U5.5
NET_U5_6: U4.10, U5.6
NET_U6_15: R11.1, U6.15
NET_U7_3: U6.7, U7.3
NET_U7_4: U6.9, U7.4
NET_U7_5: U6.6, U7.5
NET_U7_6: U6.8, U7.6
NET_U8_4: R13.1, U8.4
NET_U8_5: R12.1, U8.5
NET_U8_9: C24.2, C25.2, C26.2, R14.2, U8.9
NET_U8_15: R14.1, U8.8, U8.15
NET_U9_3: U8.12, U9.3
NET_U9_4: U8.14, U9.4
NET_U9_5: U8.11, U9.5
NET_U9_6: U8.13, U9.6
NET_U10_20: C35.1, C40.1, U10.20
NET_U11_2: C28.1, R16.1, U11.2
NET_U11_5: C27.1, R15.1, U11.5
NET_U12_5: C29.1, C30.1, R17.1, R18.1, U12.5
NET_U16_3: I1.1, U16.3
NET_U16_5: R19.1, R20.1, U16.5
NET_U16_ATNET_3: I1.2, R20.2
NET_U17_4: R21.2, R22.1, U17.4
NET_U18_5: R29.1, U18.5
NET_U18_8: R28.1, U18.8
NET_U21_1: R24.1, R25.1, U21.1
NET_U21_3: R26.2, R27.1, U21.3
NET_U21_4: R23.1, U21.4, U25.2
NET_U22_8: R30.1, U22.8
NET_U23_1: R2.1, U23.1, U23.2
PROC_I2S2_CK: U1.52, U10.7
PROC_I2S2_EXT_SD: U1.53, U10.10
PROC_I2S2_SD: U1.54, U10.8
PROC_I2S2_WS: U1.51, U10.9, U10.11
PROC_SPI1_MISO: U1.31, U6.16
PROC_SPI1_MOSI: U1.32, U6.2
PROC_SPI1_NSS: R10.1, U1.29, U6.3
PROC_SPI1_SCK: U1.30, U6.4
PROC_UART4_RX_TOXCVR: U4.19, U22.6
PROC_UART4_TX_TOXCVR: U4.14, U22.5
PROC_UART5_RX: U1.83, U2.11
PROC_UART5_TX: U1.80, U2.7
VCC_S1_3V7: C44.1, C46.1, C47.1, C52.1, U16.4, U17.5, U17.8, U18.3, U18.4, U19.1
VCC_TIER1_1V8: C1.1, C2.1, C3.1, C4.1, C5.1, C6.1, C7.1, C8.1, C12.1, C22.1, C23.1, C24.1, C31.1, C32.1, C33.1, C34.1, C36.1, C37.1, C38.1, C39.1, C41.1, C43.1, C45.2, C50.1, C55.1, C56.1, C57.1, F1.2, I1.2, R4.2, R6.2, R10.2, R11.2, R12.2, R13.2, R20.2, R23.2, R24.2, R26.1, U1.6, U1.28, U1.50, U1.75, U1.100, U2.12, U6.5, U8.7, U10.3, U10.5, U10.12, U10.18, U13.4, U15.4, U21.6, U22.2, U25.5
VCC_TIER1_3V3: C11.1, C17.1, C25.1, C26.1, C42.1, C48.1, C49.1, C53.1, C54.1, R9.2, R21.1, R30.2, U2.19, U4.26, U8.10, U14.4, U17.1, U22.7

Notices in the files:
parts and their libraries:
circuit_tree: (C) 2014 Tomasz Boleslaw CEDRO, cederom@tlen.pl, http://www.tomek.cedro.info.
